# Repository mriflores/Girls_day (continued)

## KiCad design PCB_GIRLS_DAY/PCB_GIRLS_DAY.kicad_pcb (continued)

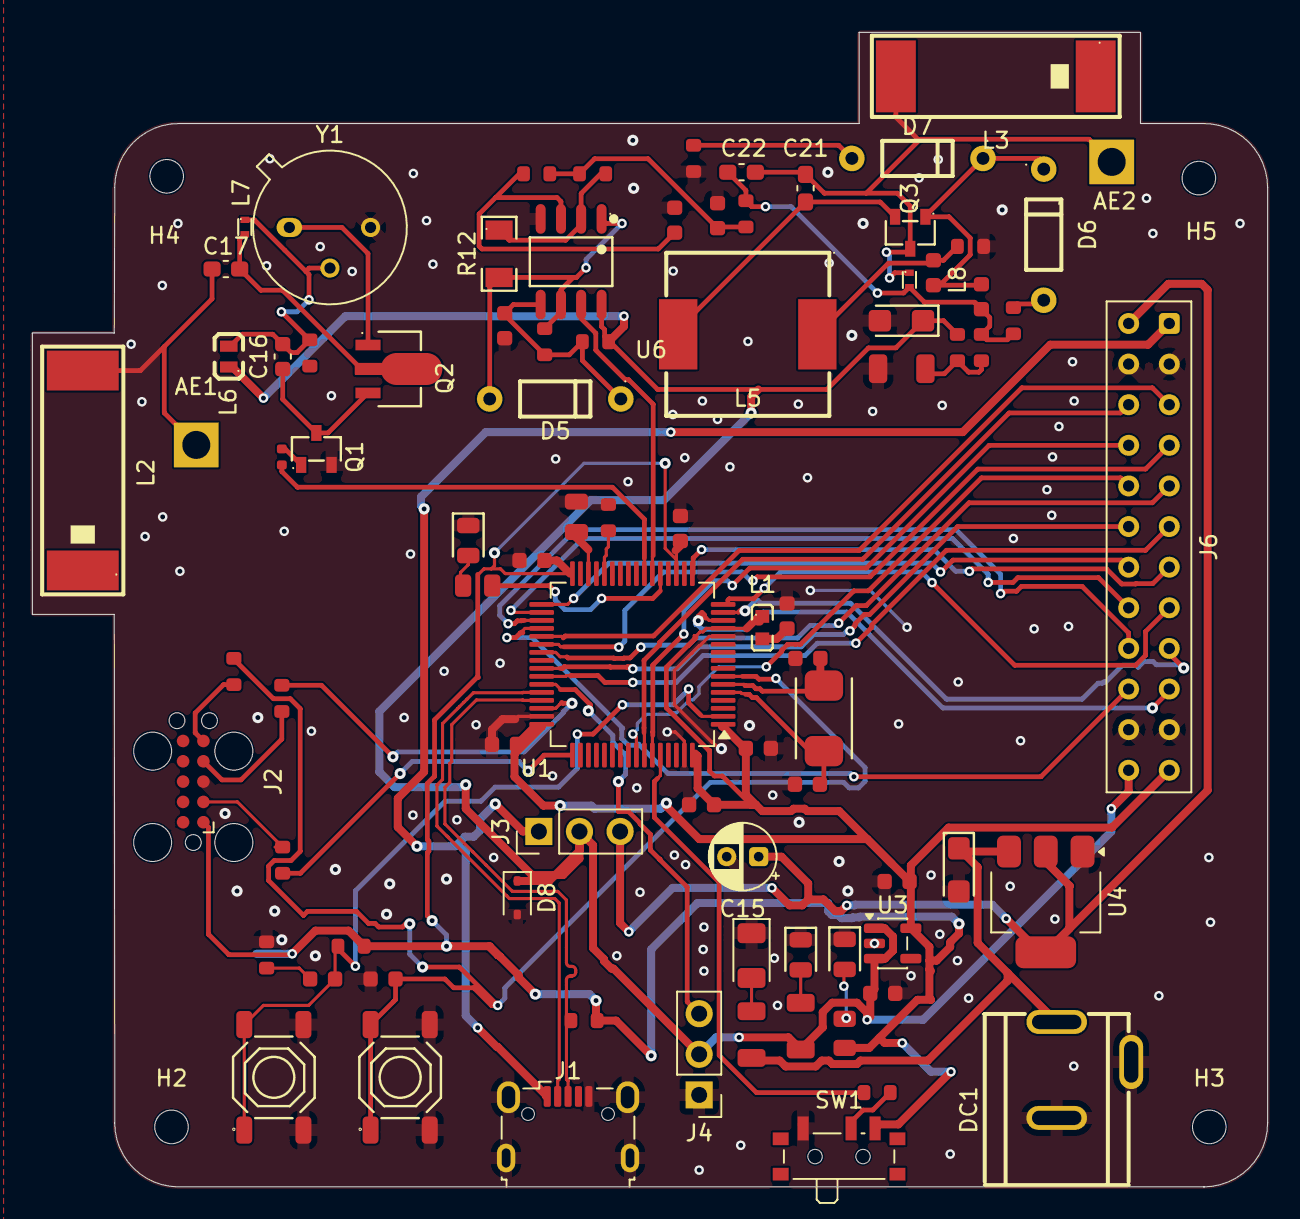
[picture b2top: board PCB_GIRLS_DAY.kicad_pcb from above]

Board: 2 copper layers, 77.2 x 72.2 mm, 90 parts (0 on the bottom side), 66 nets.

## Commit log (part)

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2026-04-02 V1_Girls_Day
2026-04-02 Initialize README with project details and setup
    Added project overview, hardware configuration, and technical implementation details to README.md.
2026-04-02 Add pro-tip for antenna wire soldering
    Added a pro-tip for improving signal resonance.
2026-04-02 Remove key concepts from README
    Removed key concepts section from README.
2026-04-02 Diagram
2026-04-02 Update README with correct hardware components
    Corrected component details and fixed typos in the README.
2026-04-17 ServoMotor
2026-04-17 Enhance README with servo control details
    Updated README to include servo control features and wiring diagrams.
2026-04-21 schematic
2026-04-22 Apply suggestion from @SeaD4wg
2026-04-22 Refactor variable names and improve message functions
2026-04-22 Rename miServo to myServo for consistency
2026-04-22 Update RF Kit and Antenna requirements in README
2026-04-22 Box in Fusion360
2026-06-02 Correct data pin descriptions in RF wiring diagram
2026-06-10 PCB_SCH
2026-06-18 Kicad - PCB avant routage
